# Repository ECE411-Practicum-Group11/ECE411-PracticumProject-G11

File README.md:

Fall 2022 ECE 411 Practicum Project 

<ins>Group 11 Team Members/Project Authors</ins> 
* Cesar Ordaz-Coronel
* Charles Nasser
* Anthony Bruno

# NERD BOX - A Handheld Video Game Console

## Description:
This practicum project is for the development of a **Handheld Video Game Console**. This gaming device has buttons for users to interact with the device electronics and view game graphics/animations on the console's display. This device was designed for beginner-electronics users who want to code their own games (also build/modify/customize their own portable game console). The handheld game console is a portabe device with a simple interface for users.

This handheld game console was designed with a simple user interface and at a affortable cost. The device contains 4 direction/navigation buttons, 2 action buttons, power switch, and a [QWIIC I2C](https://www.sparkfun.com/qwiic) connector for adding accessory sensors and devices such as an [accelerometer](https://www.sparkfun.com/products/17589) for motion control with the Handheld Video Game Console. The system uses a 3.7V 2000mah LiPo battery that is rechargable through the USB connection. The USB connection serves to not only charge the LiPo battery but also for user to upload their own coded games. This device uses the Arduino IDE (Processing language) to code games and upload/interact with the system electronics hardware. The gaming device has a 3D printed enclosure that can be modified for customized enclosure designs.

## Overview of Repository Folders/Files/Sections

* 411documents - contains all documentation for the this project over the course of 10 weeks. This folder contains Level 1 and Level 0 functional decomposition block diagrams for the device, Bill of Materials, Proposed project schedule (Ghantt Chart), Test plans, project ideas, the Product Design Specification (PDS), device electrical schematics, device PCB layout, and 3D printed CAD files.

* code - This folder contains any code that was generated to run the device, test the device, and debug the device during development. The software in this folder includes test programs, UI code for user, prototype code, and device video game code examples.

* hardware/console-hardware - This folder contains all electrical schematics, PCB layout, components, CAD project, and mechanical CAD files. This is the main folder for DIY building, fabrication, modifications, or reworking this prjoect.

* media - this folder contains all media related to this project. This includes test videos, debugging videos, test images and protoype images, demonstration videos, photos, etc.

* LICENSE file - The current license of this practicum project is CREATIVE COMMONS ZERO V1.0 UNIVERSAL. This is an Open-Source License and this project is dedicated to the public domain. This project can be copied, modified, distributed, and performance of work (including commercial purposes) without asking for permission. For more information on CC0 1.0 Universal - Public Domain Dedication, please follow this link: https://creativecommons.org/publicdomain/zero/1.0/

* README.md file - A markdown file (this file) that explains a majority of the files and folders of this practicum project. 

* Team Information - A markdown file that contains information about the team members of this practicum project.

## System Architecture - Block Diagrams
For more system architecture details, go to the [411documents](https://github.com/ECE411-Practicum-Group11/ECE411-PracticumProject-G11/tree/main/411documents) folder in this repsitory and view the [G11_L1blockDiagram](https://github.com/ECE411-Practicum-Group11/ECE411-PracticumProject-G11/blob/main/411documents/G11_L1_blockDiagram.png)

## [Demonstration & Operations Video Link](https://www.youtube.com/playlist?list=PLfQtabAE1AbKebFBLS851gg_HdHH0sS15)

## License
The current license of this practicum project is CREATIVE COMMONS ZERO V1.0 UNIVERSAL. This is an Open-Source License and this project is dedicated to the public domain. This project can be copied, modified, distributed, and performance of work (including commercial purposes) without asking for permission. For more information on CC0 1.0 Universal - Public Domain Dedication, please follow this link: https://creativecommons.org/publicdomain/zero/1.0/

## How to Download Project & Tools to Use
1) Go to the project [Repository](https://github.com/ECE411-Practicum-Group11/ECE411-PracticumProject-G11)

2) Use one of the following options

### Option 1: Download ZIP
1) Click the GREEN "<>Code" dropdown.

2) Click on "Download ZIP".

3) After the download is complete, unzip the folder using [7zip](https://www.7-zip.org/), [PeaZip](https://peazip.github.io/), [WinZip](https://www.winzip.com/en/), or any other ZIP application.

### Option 2: Git Clone
If you know how to use Git/GitHub, you can clone the project repository
1) Click the GREEN "<>Code" dropdown.

2) Copy the https git link.

3) Open git bash on your current machine and move to the directly on your local machine where you would like to clone the project repository to.

4) type the following commands.

```
git clone [the http git link you copied, you can use SHIFT + INSERT for this]
```
Now you have a local repository for this project.

You can now access all files and documents of this project

## Tools For this Project
There are a few software tools that you will need in order to build, modify, or view the files in this project.

For the PCB design schematic, PCB layout, and any other items related to the electronics board, you can use any electronics CAD design and automation software. We highly recommend using [KiCAD EDA](https://www.kicad.org/) for this project, a free, open-source electronics CAD EDA.

For the 3D Printed enclosure the project includes STL files and an AutoDesk Fusion 360 Archive file. We recommend you use [Autodesk Fusion360 CAD](https://www.autodesk.com/products/fusion-360/personal) for the 3D printed enclosure, which is free for personal use.

For software development of the device and coding your own games, we recommend you use [Arduino IDE](https://www.arduino.cc/en/software). We also recommend reading the [tutorial for the 2.8" TFT LCD](https://learn.adafruit.com/adafruit-2-8-and-3-2-color-tft-touchscreen-breakout-v2/overview). We also recommend researching some of the libraries used in the original device program for more optimization (i.e [FloppyDerp_with_UI.ino](https://github.com/ECE411-Practicum-Group11/ECE411-PracticumProject-G11/tree/main/code/FloppyDerp_with_UI))

__IMPORTANT NOTE:__ If you plan to use Arduino IDE to upload your own programs and create your own code, you MUST burn the arduino IDE Bootloader to the ATmega32U4 Microcontroller in the project. We HIGHLY recommend you use an Arduino as an ISP for burning the bootloader to the IC. You can follow a tutorial on how to set this up and the burning process at [Arduino as ISP and Arduino Bootloaders](https://docs.arduino.cc/built-in-examples/arduino-isp/ArduinoISP).

__IMPORTANT NOTE:__ If you plan to use Arduino IDE to create code and upload to the Nerd Box, PLEASE set the "Board" under "Tools" dropdown to "Arduino Leonardo"!

## POWERING THE DEVICE!
The Nerd Box has two ways to power the device:
1) Power using LiPo Battery:
The Nerd Box can be powered using a LiPo battery with a JST connector on the back of the PCB. We recommend using a 3.7V, 2000mAh battery. [This one from Adafruit](https://www.adafruit.com/product/2011) is the best since it fits in the chassis and supplies around 40 hours of power to the Nerd Box.

2) Power over USB:
The Nerd Box can also be powered directly over the USB connection. When the Nerd Box's USB is connected, if there is a LiPo battery attached then the LiPo battery will be charged up. THIS IS HOW YOU CHARGE THE LIPO BATTERY IN THE DEVICE. Again the USB serves as a way of charging the LiPo battery and programming/uploading games to the device. The Nerd Box can be powered over the USB without the LiPo battery as well.

## Assembly, Fabrication, Tests Tips & Notes

* We recommend using [Oshpark](https://oshpark.com/) to have your own PCBs fabricated and using [Digi-Key](https://www.digikey.com/) for components.
* If you have a 3D printer or printer service with fine detail/quality, you can modify the 3D enclosure with labels. Otherwise, you can use [decals](https://www.youtube.com/watch?v=YWCaCXiLDwo&t=260s&ab_channel=Tim%27sProjects) on the 3D Prints.
* The recommended screw size and type is a M2.2, self-tapping flat head screw that is roughly 16mm to 19mm in length. Here are some recommendations from McMaster-Carr: [Link 1](https://www.mcmaster.com/catalog/128/3273), [Link 2](https://www.mcmaster.com/catalog/128/3273), [Link 3](https://www.mcmaster.com/screws/tapping-wood-and-drywall-screws/18-8-stainless-steel-phillips-flat-head-screws-for-sheet-metal/screw-size~m2-2/tip-type~pointed/)
* If you are planning to assemble the PCB yourself, we recommend that you solder a subcircuit first and then test with a bench power supply, then test with the LiPo battery. This ensures that everything will operate as expected. The order we recommend from the design schematics are: 3.3V Linear Regulator, LiPo Charger, USB Input Programming & Power, ATmega32U4 + ICSP, the rest of the components. Solder the LCD LAST! Also the board contains different test points. Reference the schematic on what each one does and utilize them in your testing!
* DO NOT USE A HEAT GUN OR PCB OVEN on the PCB with the LCD soldered down to the PCB! THIS WILL DAMAGE IT!
* Consideration: If you plan to have your board fabricated & fitted/assembled by another service, we recommend you add sodler bridges between subcircuits of the device and then add 0Ohm resistors to bridge the subcircuits together. This makes testing each subcircuit easier and able to use an assembly service.
* The 3D Prints for the enclosure don't have any labels for the buttons but you are free to modify the prints with labels. You can also just add decals onto the 3D prints. Go to YouTube or read any tutorials online on how to do this.

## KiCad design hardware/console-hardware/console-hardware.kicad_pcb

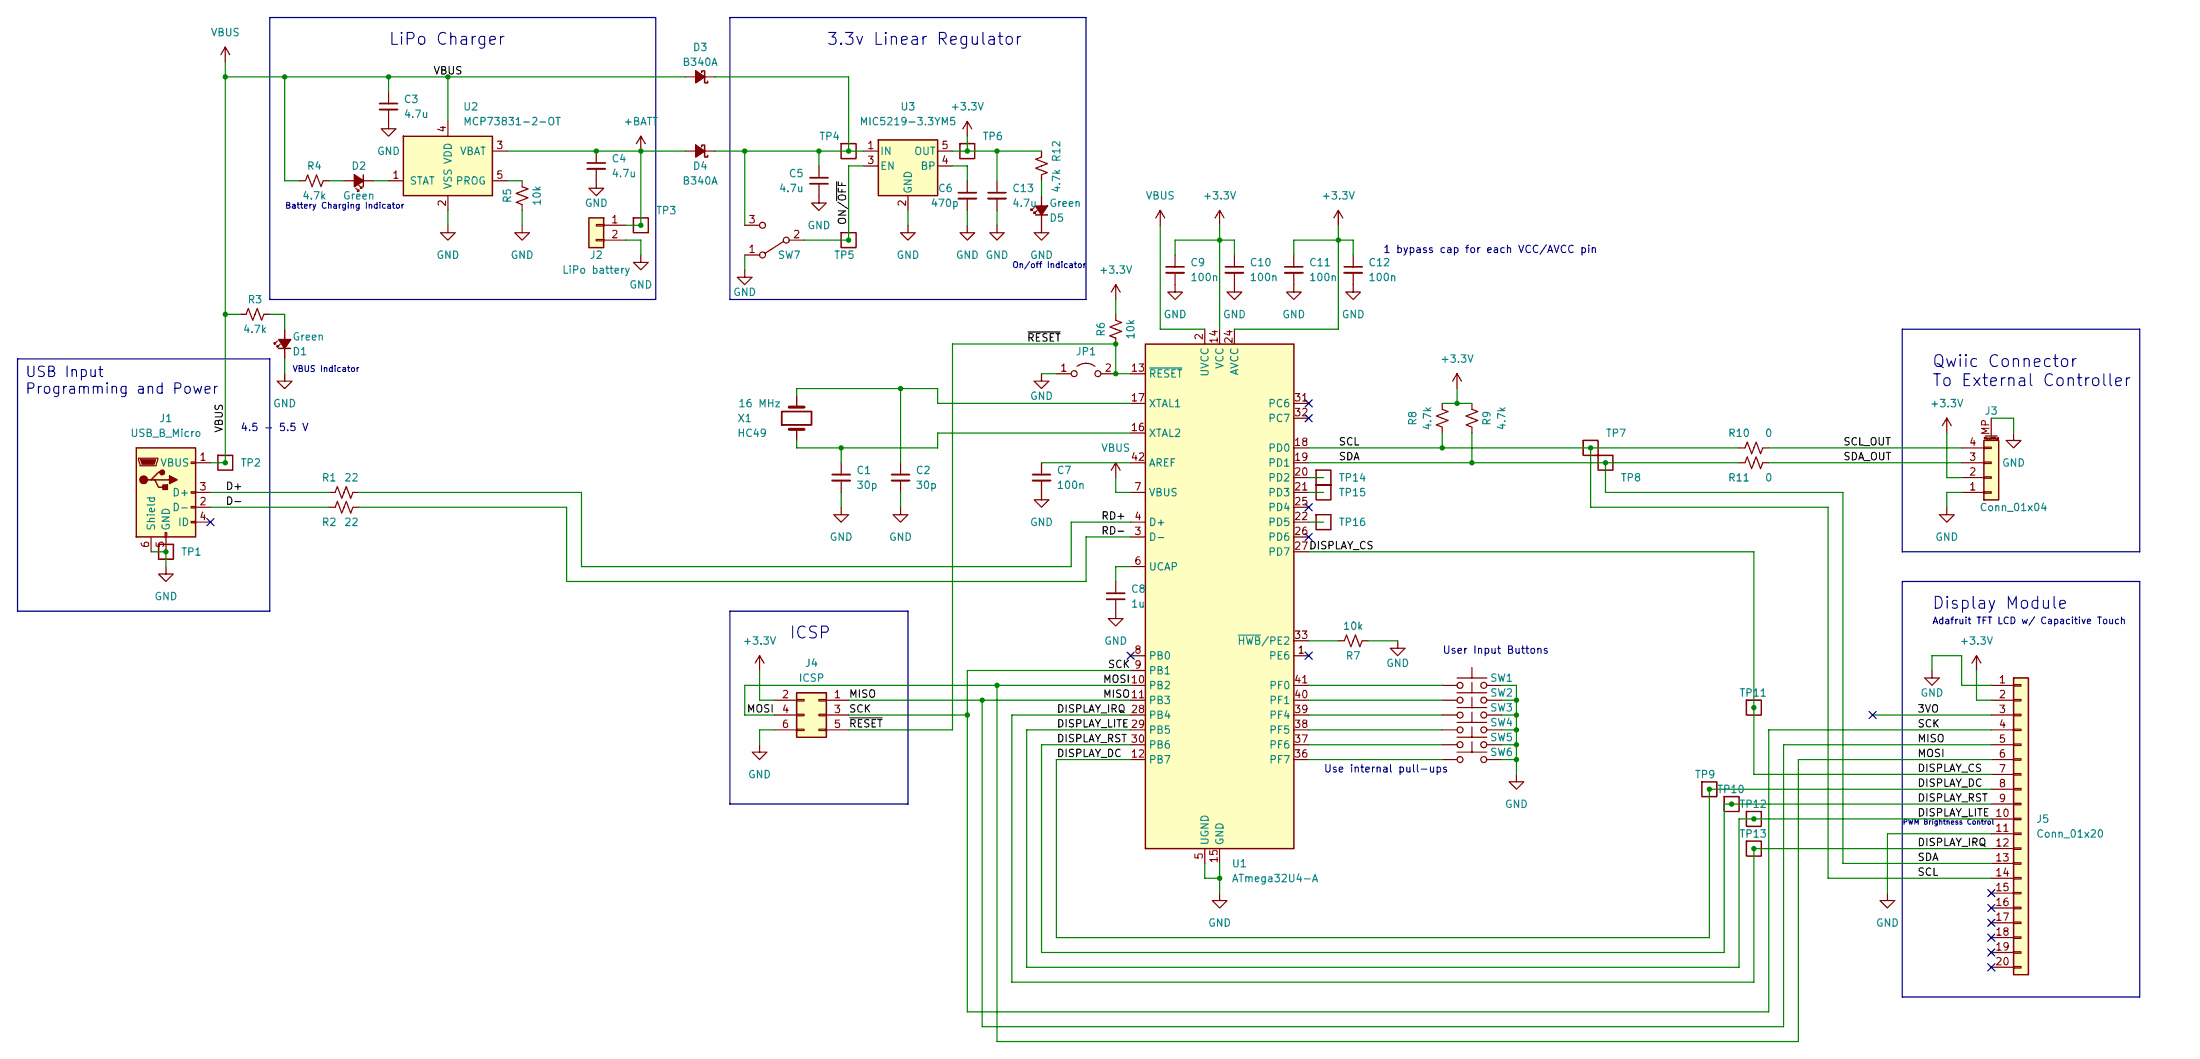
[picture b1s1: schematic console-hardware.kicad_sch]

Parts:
C1, C2: 30p; C_0805_2012Metric; MPN CML0805C0G300JT50V
C3, C4, C5, C13: 4.7u; C_0805_2012Metric; MPN CL21A475KAQNNNG
C6: 470p; C_0805_2012Metric; MPN CL21B471KBANFNC
C7, C9, C10, C11, C12: 100n; C_0805_2012Metric; MPN CL21B104KACNNNC
C8: 1u; C_0805_2012Metric; MPN CL21B105KAFNNNE
D1, D2, D5: Green; LED_0805_2012Metric; MPN SML-210MTT86
D3, D4: B340A; D_SMA; MPN B340A-M3/61T
J1: USB_B_Micro; WE_629105136821; MPN 629105136821
J2: LiPo battery; JST_PH_S2B-PH-K_1x02_P2.00mm_Horizontal; MPN S2B-PH-K-S(LF)(SN)
J3: Conn_01x04; JST_SH_SM04B-SRSS-TB_1x04-1MP_P1.00mm_Horizontal
J4: ICSP; PinHeader_2x03_P2.54mm_Vertical; MPN M20-9980346
J5: Conn_01x20; PinHeader_1x20_P2.54mm_Vertical
JP1: Jumper_2_Open; SolderJumper-2_P1.3mm_Open_Pad1.0x1.5mm
R1, R2: 22; R_0805_2012Metric; MPN RC0805FR-1322RL
R3, R4, R8, R9, R12: 4.7k; R_0805_2012Metric; MPN RC0805JR-074K7L
R5, R6, R7: 10k; R_0805_2012Metric; MPN RC0805JR-0710KL
R10, R11: 0; R_0805_2012Metric; MPN RC0805JR-070RL
SW1, SW2, SW3, SW4, SW5, SW6: SW_Push; SW_TH_Tactile_Omron_B3F-10xx; MPN B3F-1052
SW7: SW_SPDT; SW_EG1213; MPN EG1213
TP1, TP2, TP3, TP4, TP5, TP6, TP7, TP8, TP9, TP10, TP11, TP12, TP13, TP14, TP15, TP16: Test-Point; 1X01
U1: ATmega32U4-A; TQFP-44_10x10mm_P0.8mm; MPN ATMEGA32U4-AU
U2: MCP73831-2-OT; SOT-23-5; MPN MCP73831T-2DCI/OT
U3: MIC5219-3.3YM5; SOT-23-5; MPN MIC5219-3.3YM5-TR
X1: 16 MHz; Crystal_SMD_HC49-SD; MPN 830011263

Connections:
+3.3V: C9.1, C10.1, C11.1, C12.1, C13.1, J3.2, J4.2, J5.2, R6.2, R8.2, R9.2, R12.1, TP6.1, U1.14 (VCC), U1.24 (AVCC), U1.34 (VCC), U1.44 (AVCC), U3.5 (OUT)
+BATT: C4.1, D4.2 (A), J2.1, TP3.1, U2.3 (VBAT)
/3VO: J5.3
/D+: J1.3 (D+), R1.1
/D-: J1.2 (D-), R2.2
/DISPLAY_CS: J5.7, TP11.1, U1.27 (PD7)
/DISPLAY_DC: J5.8, TP9.1, U1.12 (PB7)
/DISPLAY_IRQ: J5.12, TP13.1, U1.28 (PB4)
/DISPLAY_LITE: J5.10, TP12.1, U1.29 (PB5)
/DISPLAY_RST: J5.9, TP10.1, U1.30 (PB6)
/MISO: J4.1, J5.5, U1.11 (PB3)
/MOSI: J4.4, J5.6, U1.10 (PB2)
/ON/~OFF: SW7.2 (B), TP5.1, U3.3 (EN)
/RD+: R1.2, U1.4 (D+)
/RD-: R2.1, U1.3 (D-)
/SCK: J4.3, J5.4, U1.9 (PB1)
/SCL: J5.14, R8.1, R10.2, TP7.1, U1.18 (PD0)
/SCL_OUT: J3.4, R10.1
/SDA: J5.13, R9.1, R11.1, TP8.1, U1.19 (PD1)
/SDA_OUT: J3.3, R11.2
/~RESET: J4.5, JP1.2 (B), R6.1, U1.13 (~RESET)
GND: C1.2, C2.2, C3.2, C4.2, C5.2, C6.2, C7.2, C8.2, C9.2, C10.2, C11.2, C12.2, C13.2, D1.1 (K), D5.1 (K), J1.5 (GND), J1.6 (Shield), J2.2, J3.1, J3.MP (MountPin), J4.6, J5.1, J5.11, JP1.1 (A), R5.1, R7.1, SW1.2, SW2.2, SW3.2, SW4.2, SW5.2, SW6.2, SW7.1 (A), TP1.1, U1.5 (UGND), U1.15 (GND), U1.23 (GND), U1.35 (GND), U1.43 (GND), U2.2 (VSS), U3.2 (GND)
unnamed: C1.1, U1.16 (XTAL2), X1.1
unnamed: C2.1, U1.17 (XTAL1), X1.2
unnamed: C5.1, D3.1 (K), D4.1 (K), SW7.3 (C), TP4.1, U3.1 (IN)
unnamed: C6.1, U3.4 (BP)
unnamed: C7.1, U1.42 (AREF)
unnamed: C8.1, U1.6 (UCAP)
unnamed: D1.2 (A), R3.2
unnamed: D2.1 (K), U2.1 (STAT)
unnamed: D2.2 (A), R4.2
unnamed: D5.2 (A), R12.2
unnamed: R5.2, U2.5 (PROG)
unnamed: R7.2, U1.33 (~HWB/PE2)
unnamed: SW1.1, U1.41 (PF0)
unnamed: SW2.1, U1.40 (PF1)
unnamed: SW3.1, U1.39 (PF4)
unnamed: SW4.1, U1.38 (PF5)
unnamed: SW5.1, U1.37 (PF6)
unnamed: SW6.1, U1.36 (PF7)
unnamed: TP14.1, U1.20 (PD2)
unnamed: TP15.1, U1.21 (PD3)
unnamed: TP16.1, U1.22 (PD5)
VBUS: C3.1, D3.2 (A), J1.1 (VBUS), R3.1, R4.1, TP2.1, U1.2 (UVCC), U1.7 (VBUS), U2.4 (VDD)

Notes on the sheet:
3.3v Linear Regulator
Battery Charging Indicator
ICSP
Qwiic Connector To External Controller
PWM Brightness Control
On/off Indicator
VBUS Indicator
USB Input Programming and Power
Display Module
LiPo Charger
4.5 - 5.5 V
Adafruit TFT LCD w/ Capacitive Touch
Use internal pull-ups
1 bypass cap for each VCC/AVCC pin
User Input Buttons

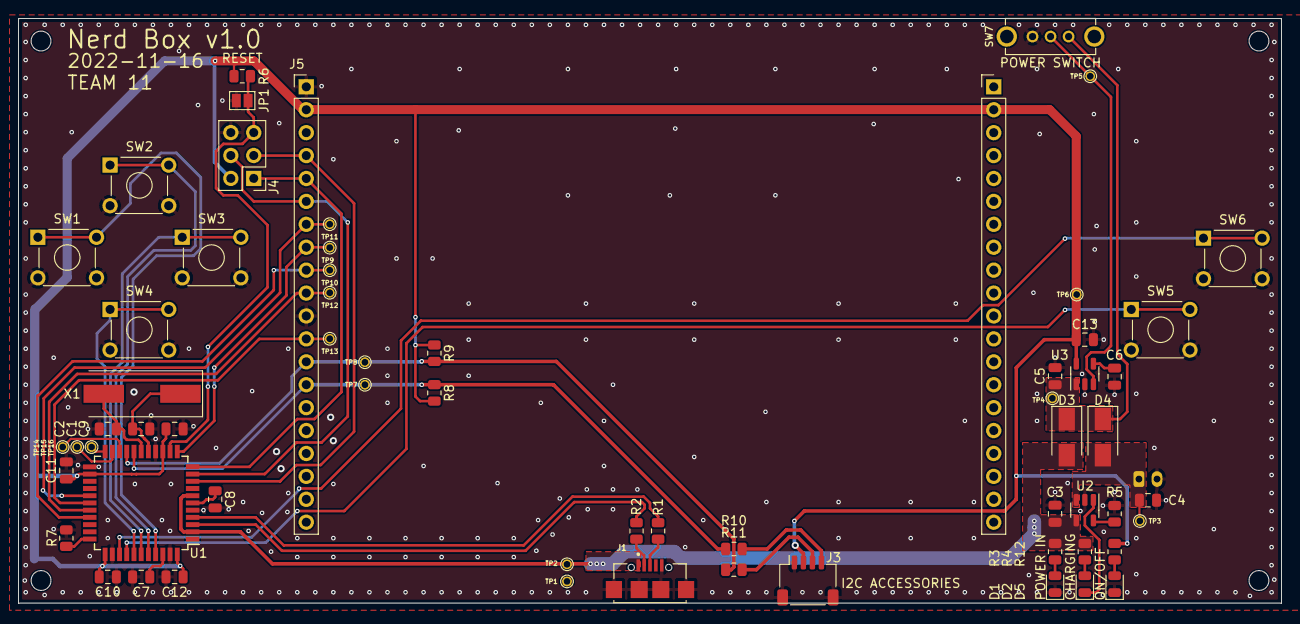
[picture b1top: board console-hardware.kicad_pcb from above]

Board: 2 copper layers, 140.0 x 64.8 mm, 63 parts (1 on the bottom side), 43 nets.

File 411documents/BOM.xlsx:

Bill Of Materials for: Team 11
Last modified: 12/06/2022 |  |  | TOTAL DEVICE COST |  | 81.1
PCB version: 1.0
BOM revision: 3 |  | P/NP | = Place/Not Place (components marked NP are not stuffed on the board)
Qty | References | P/DNP | MFR | MPN | Description | Dist | DPN | price per unit | Total cost | Availability | Ordered | Received
2.0 | C1, C2, | P | Stackpole | CML0805C0G300JT50V | 30 pF 0806 Ceramic capacitor | Digi-Key | 738-CML0805C0G300JT50VCT-ND | 0.1 | 0.2 | 1 | 1 | 1
4.0 | C3, C4, C5, C13 | P | Samsung | CL21A475KAQNNNG | 4.7 uF 0806 Ceramic capacitor | Digi-Key | 1276-6462-1-ND | 0.1 | 0.4 | 1 | 1 | 1
1.0 | C6, | P | Samsung | CL21B471KBANFNC | 470 nF 0806 Ceramic capacitor | Digi-Key | 1276-2515-1-ND | 0.1 | 0.1 | 1 | 1 | 1
5.0 | C7, C9, C10, C11, C12, | P | Samsung | CL21B104KACNNNC | 100 nF 0806 Ceramic capacitor | Digi-Key | 1276-1099-1-ND | 0.1 | 0.5 | 1 | 1 | 1
1.0 | C8, | P | Samsung | CL21B105KAFNNNE | 1 uF 0806 Ceramic capacitor | Digi-Key | 1276-1066-1-ND | 0.1 | 0.1 | 1 | 1 | 1
3.0 | D1, D2, D5, | P | Rohm | SML-210MTT86 | Green 0806 LED | Digi-Key | 511-1287-1-ND | 0.37 | 1.11 | 1 | 1 | 1
2.0 | D3, D4, | P | Vishay | B340A-M3/61T | Schottky diode | Digi-Key | B340A-M3/61TGICT-ND | 0.43 | 0.86 | 1 | 1 | 1
1.0 | J1, | P | Wurth | 6.29105136821E11 | USB Micro Type B connector | Digi-Key | 732-3155-1-ND | 1.29 | 1.29 | 1 | 1 | 1
1.0 | J2, | P | JST | S2B-PH-K-S(LF)(SN) | LiPo battery connector | Digi-Key | 455-1719-ND | 0.17 | 0.17 | 1 | 1 | 1
1.0 | J3, | P |  | 10147606-00004LF | 4 pin JST connector | Digi-Key | 609-6302-1-ND | 0.67 | 0.67 | 1 | 1 | 1
1.0 | J4, | P | Harwin | M20-9980346 | 2x3 2.54mm Pin header | Digi-Key | 952-2121-ND | 0.3 | 0.3 | 1 | 1 | 1
1.0 | J5, | P | Adafruit |  | 2.8" TFT LCD with Cap Touch Breakout Board | Adafruit | 2090.0 | 39.95 | 39.95 | 1 | 1 | 1
2.0 | R1, R2, | P | Yageo | RC0805FR-1322RL | 22 Ohm 0806 resistor | Digi-Key | 13-RC0805FR-1322RLCT-ND | 0.1 | 0.2 | 1 | 1 | 1
5.0 | R3, R4, R8, R9, R12, | P | Yageo | RC0805JR-074K7L | 4.7k 0806 resistor | Digi-Key | 311-4.7KARCT-ND | 0.1 | 0.5 | 1 | 1 | 1
3.0 | R5, R6, R7, | P | Yageo | RC0805JR-0710KL | 10k 0806 resistor | Digi-Key | 311-10KARCT-ND | 0.1 | 0.3 | 1 | 1 | 1
2.0 | R10, R11, | P | Yageo | RC0805JR-070RL | 0 ohm 0806 resistor | Digi-Key | 311-0.0ARCT-ND | 0.1 | 0.2 | 1 | 1 | 1
6.0 | SW1, SW2, SW3, SW4, SW5, SW6, | P | Omron | B3F-1052 | Tactile Switch | Digi-Key | SW405-ND | 0.38 | 2.28 | 1 | 1 | 1
1.0 | SW7, | P | E-Switch | EG1213 | SPDT slide switch | Digi-Key | EG1906-ND | 0.76 | 0.76 | 1 | 1 | 1
1.0 | U1, | P | Microchip | ATMEGA32U4-AU | ATMEGA32U4 microcontroller | Digi-Key | ATMEGA32U4-AU-ND | 5.68 | 5.68 | 1 | 1 | 1
1.0 | U2, | P | Microchip | MCP73831T-2DCI/OT | Single cell, Li-Ion/Li-Po charge management controller, 4.20V, Tri-State Status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 | Digi-Key | MCP73831T-2DCI/OTCT-ND | 0.76 | 0.76 | 1 | 1 | 1
1.0 | U3, | P | Microchip | MIC5219-3.3YM5-TR | 500mA low dropout linear regulator, fixed 3.3V output, SOT-23-5 | Digi-Key | 576-1281-1-ND | 1.2 | 1.2 | 1 | 1 | 1
1.0 | X1, | P | Wurth | 8.30011263E8 | 16 MHz crystal | Digi-Key | 1923-830011263CT-ND | 0.35 | 0.35 | 1 | 1 | 1
6.0 | - | DNP | Omron | B32-2010 | Button cap | Digi-Key | SW1139-ND | 0.94 | 5.64 | 1 | 1 | 1
1.0 | - | DNP |  |  | Printed Circuit Board for Nerd Box design | - |  | 17.58 | 17.58 | 1 | 1 | 1
 |  |  |  |  |  |  |  |  | 0.0
 |  |  |  |  |  |  | TOTAL DEVICE COST |  | 81.1

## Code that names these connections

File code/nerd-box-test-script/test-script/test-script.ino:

// Script for testing hardware functionality of the Nerd Box console
// Writes text to the display and serial monitor corresponding to each hardware button when pressed

// Display libraries
#include <SPI.h>
#include <Adafruit_GFX.h>
#include <Adafruit_ILI9341.h>

// Pin number macro definitions
#define DISPLAY_CS 6
#define DISPLAY_DC 11
#define DISPLAY_RST 10

#define DISPLAY_LITE 9

#define BUTTON_LEFT A5
#define BUTTON_UP A4
#define BUTTON_RIGHT A3
#define BUTTON_DOWN A2
#define BUTTON_A A1
#define BUTTON_B A0

// Initialize display object
Adafruit_ILI9341 tft = Adafruit_ILI9341(DISPLAY_CS, DISPLAY_DC, MOSI, SCK, DISPLAY_RST, MISO);

void setup() {
  delay(100);
  Serial.begin(19200);
  pinMode(DISPLAY_LITE, OUTPUT);
  analogWrite(DISPLAY_LITE, 30);
  tft.begin();
  
  // Print debug text to serial monitor and dispaly
  Serial.println("Nerd Box test script v1.0");  
  tft.setRotation(3);
  tft.fillScreen(0x0000);
  tft.setCursor(20, 20); // Cursor near top left corner
  tft.setTextColor(0xF800, 0x0000); // Red with black fill
  tft.println("Nerd Box test script v1.0");
  tft.println();

  // Initialize user button inputs
  pinMode(BUTTON_LEFT, INPUT_PULLUP);
  pinMode(BUTTON_UP, INPUT_PULLUP);
  pinMode(BUTTON_RIGHT, INPUT_PULLUP);
  pinMode(BUTTON_DOWN, INPUT_PULLUP);
  pinMode(BUTTON_A, INPUT_PULLUP);
  pinMode(BUTTON_B, INPUT_PULLUP);
}


// Storing button states for debouncing
byte upPress = LOW;
byte rightPress = LOW;
byte downPress = LOW;
byte leftPress = LOW;
byte aPress = LOW;
byte bPress = LOW;

// Storing time when buttons pressed for debouncing
unsigned long upTime = 0;
unsigned long rightTime = 0;
unsigned long downTime = 0;
unsigned long leftTime = 0;
unsigned long aTime = 0;
unsigned long bTime = 0;

void loop() {
  // Check button inputs
  // Print button name to serial monitor and display when pressed

  if (checkButton(BUTTON_UP, &upPress, &upTime)) {
    Serial.println("Up");
    tft.println("Up      ");
  }

  if (checkButton(BUTTON_RIGHT, &rightPress, &rightTime)) {
    Serial.println("Right");
    tft.println("Right  ");
  }

  if (checkButton(BUTTON_DOWN, &downPress, &downTime)) {
    Serial.println("Down");
    tft.println("Down   ");
  }

  if (checkButton(BUTTON_LEFT, &leftPress, &leftTime)) {
    Serial.println("Left");
    tft.println("Left    ");
  }

  if (checkButton(BUTTON_A, &aPress, &aTime)) {
    Serial.println("A");
    tft.println("A       ");
  }

  if (checkButton(BUTTON_B, &bPress, &bTime)) {
    Serial.println("B");
    tft.println("B      ");
  }

}

byte checkButton(int pinNumber, byte *buttonPress, unsigned long *buttonTime) {
  // Reads button press with debounce timer, based on debounce routine from arduino docs
  // buttonPress is the current state of the input, buttonTime is the time when the button state last changed from millis()
  // Pass pointers to variables containing button state and time

  byte buttonInput = digitalRead(pinNumber);
  if (*buttonPress != buttonInput) {
    // Record last time button pressed/released
    *buttonTime = millis();
  }

  if ((millis() - *buttonTime) > 50) {
    // Change button state after debounce period
    *buttonPress = buttonInput;

      if(*buttonPress == LOW) {
        // Return true if button is pressed after debounce period
        tft.setCursor(20, 40);
        return 1;
      }
  }

  // Returns false if button state was not changed to HIGH
  return 0;
}

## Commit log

2022-10-11 created team info file
2022-10-11 updated team_info.md
    added names, need team members to add their own information.
2022-10-11 added underlines
2022-10-14 uploaded Team11 Project Ideas
2022-10-19 uploaded ideas
2022-10-20 Create .gitignore
    Ignore KiCad files
2022-10-21 Added some test code for making a ball jump on an LCD
2022-10-24 Updated ball test code, and added code for detecting a shake with the imu, and making the ball jump with the imu
2022-10-24 Created KiCad schematic for hardware
2022-10-26 Added 3.3v regulator and LiPo charger and more
2022-10-27 Added buttons and display to schematic, plus some other changes
2022-11-03 Created prototype directory
2022-11-03 Updated prototype readme to include image
2022-11-03 Actually updated prototype readme for real this time
2022-11-03 Updated schematic and added preliminary layout
2022-11-07 Added test file
2022-11-07 Removed test file
2022-11-10 block diagrams
    L0 and L1 block diagrams for ECE 411 practicum project
2022-11-10 Updated schematic and layout. Added BOM
2022-11-14 Updated board layout, some small schematic fixes, and added 3D models
2022-11-15 testing github
2022-11-17 Updated board, fixed drc errors, added mounting holes and test points, added name
2022-11-17 Finishing touches to the PCB. Updated attributes for parts.
2022-11-29 Added test plan
2022-11-30 Added script for testing console hardware
2022-12-02 Modified test script pin assignments, and background color/rotation
2022-12-02 Added test script version that uses PDQ_GFX library which is faster
2022-12-02 Fixed pin assignments and looping bug
2022-12-04 added STL files for enclosure
2022-12-04 added PCB 3D render view
2022-12-04 added png of block diagram 0
2022-12-05 Added FloppyDerp
2022-12-06 Added functionality to floppy derp
2022-12-08 Updated code and combined game with UI
